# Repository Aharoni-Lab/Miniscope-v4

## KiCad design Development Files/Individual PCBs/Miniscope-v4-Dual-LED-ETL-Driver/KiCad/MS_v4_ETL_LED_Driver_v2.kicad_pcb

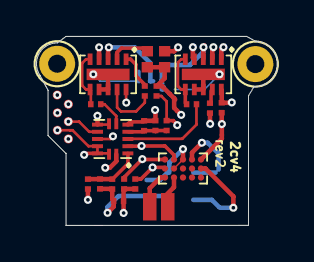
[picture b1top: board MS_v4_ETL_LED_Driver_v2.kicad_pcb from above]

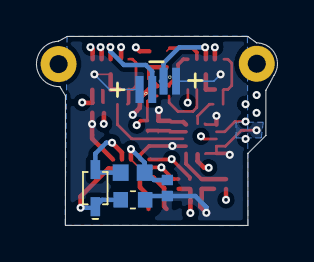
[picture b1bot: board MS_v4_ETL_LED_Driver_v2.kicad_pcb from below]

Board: 6 copper layers, 13.4 x 10.5 mm, 31 parts (6 on the bottom side), 24 nets.

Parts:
C1, C6, C10: GRM155R60J475ME87D; C_0402_1005Metric_L
C2, C5, C8, C9: GRM033R61A225ME47D; C_0201_0603Metric_L
C3: 100nF 100V 0603; C_0603_1608Metric_L
C4, C7, C11: GRM033R61A104ME15D; C_0201_0603Metric_L
D1: BAS316; SOD_323_250X125X110L30X32L
D2: LXZ1-PR01; LED_LXZ1_PR01_L
D3: LXZ1-PR01 (Yellow); LED_LXZ1_PR01_L
H1: MountingHole_Pad; Conn_1x1_700_Circular_Pad
J6, J7: Conn_01x01; Conn_1x1_250x750_Pad
J10: Conn_01x05; B2B_Flex_05_Dual_Row_38milx24mil_Pad_20mil
L1: LQM18PN3R3MGHD; L_0603_1608Metric_L
R1, R4: ERJ-1GEF1022C; R_0201_0603Metric_ERJ_L
R2, R3: DNL; R_0201_0603Metric_ERJ_L
R5, R7: ERJ-1GNJ622C; R_0201_0603Metric_ERJ_L
R6, R8: ERJ-1GEF3741C; R_0201_0603Metric_ERJ_L
U1: MAX14574EWL+; BGA_15_NP50_3X5_155X255X69B31N
U2: TPL0102-100RUCR; QFN_14_P40_200X200X40L40X20L
U3, U4: LTC3218; SON_11_P50_300X200X80L40X25T239X64L

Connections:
+3V3: C1.1, C2.1, C4.1, C8.1, J10.5, L1.1, R2.2, R3.2, R5.1, R7.1, U1.A3, U1.B2, U2.14, U3.10, U4.10
/ENT1: J10.1, U3.4
/ENT2: H1.1, U4.4
/EWL1: J6.1, U1.C2
/EWL2: J7.1, U1.C1
/SCL: J10.2, R3.1, U1.B1, U2.10
/SDA: J10.3, R2.1, U1.A1, U2.9
/Va: C7.1, R5.2, R6.1, U2.1
/Vb: C11.1, R7.2, R8.1, U2.4
/_Wa: R4.1, U2.3
/_Wb: R1.1, U2.6
GND: C1.2, C2.2, C3.2, C4.2, C6.2, C7.2, C8.2, C10.2, C11.2, D2.C, D3.C, J10.4, R6.2, R8.2, U1.A2, U1.A5, U2.2, U2.5, U2.7, U2.8, U2.11, U2.12, U2.13, U3.7, U3.8, U3.11, U4.7, U4.8, U4.11
unnamed: C3.1, D1.C, U1.B5
unnamed: C5.1, U3.9
unnamed: C5.2, U3.1
unnamed: C6.1, U3.2
unnamed: C9.1, U4.9
unnamed: C9.2, U4.1
unnamed: C10.1, U4.2
unnamed: D1.A, L1.2, U1.A4
unnamed: D2.A, U3.3
unnamed: D3.A, U4.3
unnamed: R1.2, U3.5, U3.6
unnamed: R4.2, U4.5, U4.6

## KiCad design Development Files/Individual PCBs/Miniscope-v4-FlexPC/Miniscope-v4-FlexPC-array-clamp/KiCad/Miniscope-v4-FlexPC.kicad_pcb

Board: 2 copper layers, 6 parts (0 on the bottom side), 31 nets.

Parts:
J1, J2: Conn_01x20; B2B_Flex_20_Dual_Row_38milx24mil_Hole_10milx20mil_Clearance
J3, J4: Conn_01x05; B2B_Flex_05_Dual_Row_38milx24mil_Hole_20_Clearance
J5, J6: Conn_01x14; B2B_Flex_14_Dual_Row_38milx24mil_Hole_10milx20mil_Clearance

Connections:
unnamed: J1.2, J2.2
unnamed: J1.3, J2.3
unnamed: J1.4, J2.4
unnamed: J1.5, J2.5
unnamed: J1.6, J2.6
unnamed: J1.7, J2.7
unnamed: J1.8, J2.8
unnamed: J1.9, J2.9
unnamed: J1.10, J2.10
unnamed: J1.11, J2.11
unnamed: J1.12, J2.12
unnamed: J1.13, J2.13
unnamed: J1.14, J2.14
unnamed: J1.15, J2.15
unnamed: J1.16, J2.16
unnamed: J1.17, J2.17
unnamed: J1.18, J2.18
unnamed: J1.19, J2.19
unnamed: J1.20, J2.20
unnamed: J5.2, J6.2
unnamed: J5.4, J6.4
unnamed: J5.5, J6.5
unnamed: J5.6, J6.6
unnamed: J5.7, J6.7
unnamed: J5.8, J6.8
unnamed: J5.9, J6.9
unnamed: J5.10, J6.10
unnamed: J5.11, J6.11
unnamed: J5.12, J6.12
unnamed: J5.13, J6.13
unnamed: J5.14, J6.14
